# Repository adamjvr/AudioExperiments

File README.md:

# AudioExperiments
Audio Circuit Experiments, mostly two layer audio thingys..................

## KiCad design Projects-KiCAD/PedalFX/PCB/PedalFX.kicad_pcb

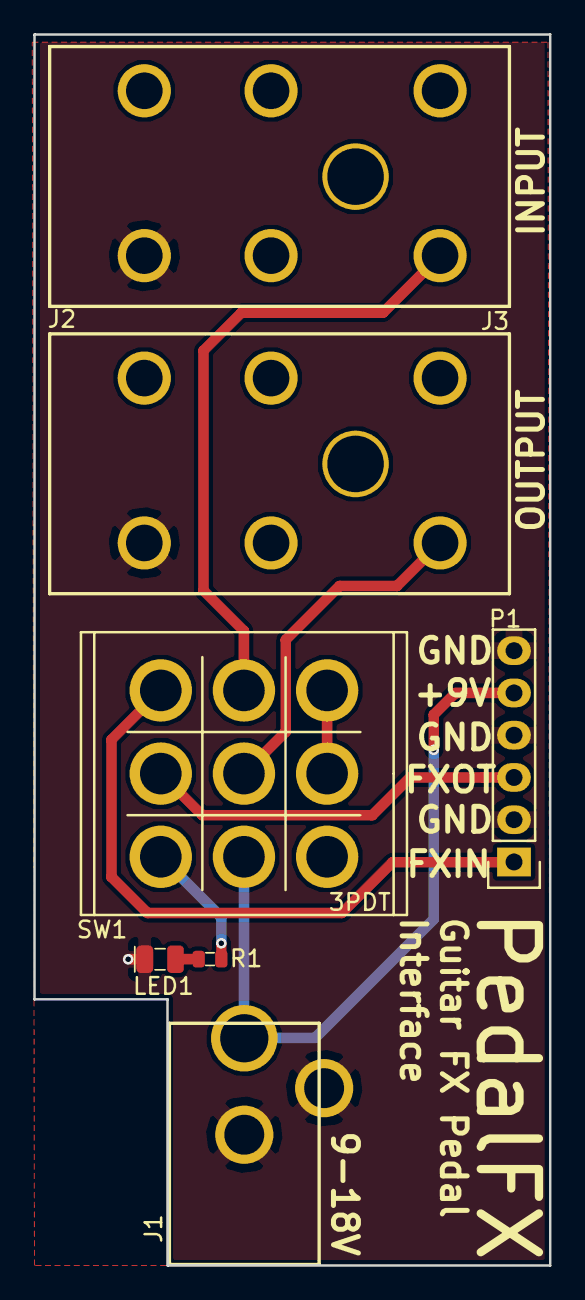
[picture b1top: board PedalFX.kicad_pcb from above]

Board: 2 copper layers, 31.0 x 74.0 mm, 7 parts (0 on the bottom side), 9 nets.

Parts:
J1: 694106301002
J2, J3: RA49C12B
LED1: 5988140107F; LED0805Y
P1: CONN_01X06; Pin_Header_Straight_1x06
R1: ERJ-3EKF1001V; R0603
SW1: 3PDT; Switches_Stomp_Switch_3PDT

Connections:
+9V: J1.1, P1.5, SW1.8
/BYPASS: SW1.3, SW1.6
/FX_IN: P1.1, SW1.1
/FX_OUT: P1.3, SW1.4
/INPUT: J2.1, SW1.2
/OUTPUT: J3.1, SW1.5
GND: J1.2, J1.3, J2.3, J3.3, LED1.2, P1.2, P1.4, P1.6
unnamed: LED1.1, R1.1
unnamed: R1.2, SW1.7

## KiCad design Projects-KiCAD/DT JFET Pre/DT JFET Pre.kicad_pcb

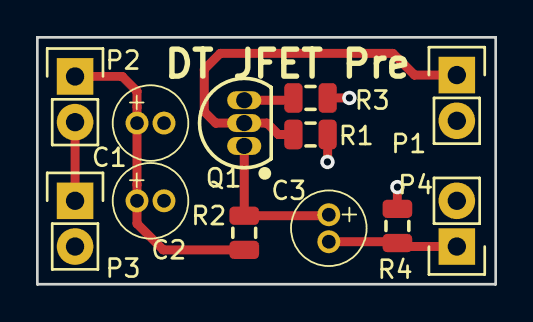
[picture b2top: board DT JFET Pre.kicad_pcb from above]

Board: 2 copper layers, 25.5 x 13.7 mm, 12 parts (0 on the bottom side), 7 nets.

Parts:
C1, C2: UMW1C100MDD1TP; UMW1V4R7MDD1TP
C3: UMW1V4R7MDD1TP
P1, P2, P3, P4: CONN_01X02; Pin_Header_Straight_1x02
Q1: 2N5457
R1: RC2012F305CS; R0805
R2: RC2012F682CS; R0805
R3: RC2012F222CS; R0805
R4: RC2012F513CS; R0805

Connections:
+9V: C1.1, C2.1, P2.1, R2.1
GND: C1.2, C2.2, P1.2, P3.2, P4.2, R1.2, R3.2, R4.2
unnamed: C3.1, Q1.1, R2.2
unnamed: C3.2, P4.1, R4.1
unnamed: P1.1, Q1.2, R1.1
unnamed: P2.2, P3.1
unnamed: Q1.3, R3.1

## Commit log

2016-05-11 Footprints
    Ton more footprints added for a large array of components for future
    audio designs. uPre redesign, overdriver experiments, and three band
    tone control.
2016-05-11 More Footprints and Projects
    Completed schematic for DT JFET Pre, Big muff clipping stage, and nearly
    finished advanced tone control. More components added to the libraries.
2016-10-11 Lost Files
    Lost files recovered from laptop backup, completed PCBs for DT JFET Pre
    and tone control added.
2016-10-18 3D Data and PedalFX
    more parts and 3D data added to the project library. PedalFX board
    designed and completed.
2019-11-30 backup
    backup
